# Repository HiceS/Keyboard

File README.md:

# Keyboard
Keyboard pcb

## Description
Uses ` 104 ` key keyboard design, can be shortened

    ["Esc",{x:1},"F1","F2","F3","F4",{x:0.5},"F5","F6","F7","F8",{x:0.5},"F9","F10","F11","F12",{x:0.25},"PrtSc","Scroll Lock","Pause\nBreak"],
    [{y:0.5},"~\n`","!\n1","@\n2","#\n3","$\n4","%\n5","^\n6","&\n7","*\n8","(\n9",")\n0","_\n-","+\n=",{w:2},"Backspace",{x:0.25},"Insert","Home","PgUp",{x:0.25},"Num Lock","/","*","-"],
    [{w:1.5},"Tab","Q","W","E","R","T","Y","U","I","O","P","{\n[","}\n]",{w:1.5},"|\n\\",{x:0.25},"Delete","End","PgDn",{x:0.25},"7\nHome","8\n↑","9\nPgUp",{h:2},"+"],
    [{w:1.75},"Caps Lock","A","S","D","F","G","H","J","K","L",":\n;","\"\n'",{w:2.25},"Enter",{x:3.5},"4\n←","5","6\n→"],
    [{w:2.25},"Shift","Z","X","C","V","B","N","M","<\n,",">\n.","?\n/",{w:2.75},"Shift",{x:1.25},"↑",{x:1.25},"1\nEnd","2\n↓","3\nPgDn",{h:2},"Enter"],
    [{w:1.25},"Ctrl",{w:1.25},"Win",{w:1.25},"Alt",{a:7,w:6.25},"",{a:4,w:1.25},"Alt",{w:1.25},"Win",{w:1.25},"Menu",{w:1.25},"Ctrl",{x:0.25},"←","↓","→",{x:0.25,w:2},"0\nIns",".\nDel"]

#### Example Layout

#### Plans to have:
- Fusion 360 Case and Board Design
- Generative Design Case
- Stress Simulations

## How to use
The ` .brd ` & ` .sch ` Files are from **Autodesk Eagle**

Open the parent folder in Eagle and you can see the schematic and board design.

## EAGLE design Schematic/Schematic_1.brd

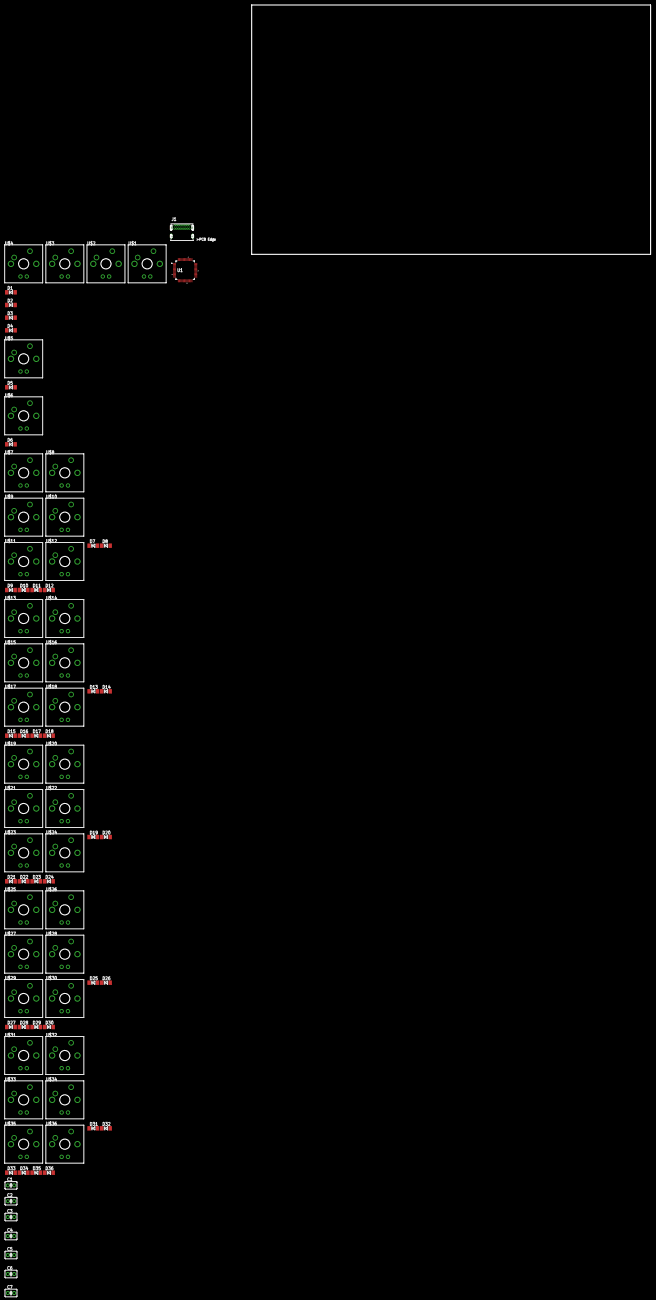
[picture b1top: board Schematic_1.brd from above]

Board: 2 copper layers, 192.6 x 100.0 mm, 81 parts (0 on the bottom side), 54 nets, no tracks yet.

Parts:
C1, C2, C4: 100 nF; C2.5-3
C3, C5: 4.7 mF; C2.5-3
C6: 10 nF; C2.5-3
C7: 1 mF; C2.5-3
D1, D2, D3, D4, D5, D6, D7, D8, D9, D10, D11, D12, D13, D14, D15, D16, D17, D18, D19, D20, D21, D22, D23, D24, D25, D26, D27, D28, D29, D30, D31, D32, D33, D34, D35, D36: SOD80C
J1: USB4085-GF-A_REVA; GCT_USB4085-GF-A_REVA
U1: STM32F0XXC2T; LQFP48-7X7MM
U$1, U$2, U$3, U$4, U$5, U$6, U$7, U$8, U$9, U$10, U$11, U$12, U$13, U$14, U$15, U$16, U$17, U$18, U$19, U$20, U$21, U$22, U$23, U$24, U$25, U$26, U$27, U$28, U$29, U$30, U$31, U$32, U$33, U$34, U$35, U$36: CHERRY-MX-LED

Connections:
COL1: D1.C, D2.C, D3.C, D4.C, D5.C, D6.C, U1.41
COL2: D7.C, D8.C, D9.C, D10.C, D11.C, D12.C, U1.40
COL3: D13.C, D14.C, D15.C, D16.C, D17.C, D18.C, U1.39
COL4: D19.C, D20.C, D21.C, D22.C, D23.C, D24.C, U1.20
COL5: D25.C, D26.C, D27.C, D28.C, D29.C, D30.C, U1.19
COL6: D31.C, D32.C, D33.C, D34.C, D35.C, D36.C, U1.18
unnamed: D2.A, U$1.SW2
unnamed: D1.A, U$3.SW2
unnamed: D3.A, U$4.SW2
unnamed: D6.A, U$6.SW2
unnamed: D8.A, U$7.SW2
unnamed: D4.A, U$2.SW2
unnamed: D5.A, U$5.SW2
unnamed: D7.A, U$9.SW2
unnamed: D9.A, U$10.SW2
unnamed: D10.A, U$8.SW2
unnamed: D11.A, U$11.SW2
unnamed: D12.A, U$12.SW2
unnamed: D14.A, U$13.SW2
unnamed: D13.A, U$15.SW2
unnamed: D15.A, U$16.SW2
unnamed: D16.A, U$14.SW2
unnamed: D17.A, U$17.SW2
unnamed: D18.A, U$18.SW2
unnamed: D20.A, U$19.SW2
unnamed: D19.A, U$21.SW2
unnamed: D21.A, U$22.SW2
unnamed: D22.A, U$20.SW2
unnamed: D23.A, U$23.SW2
unnamed: D24.A, U$24.SW2
unnamed: D26.A, U$25.SW2
unnamed: D25.A, U$27.SW2
unnamed: D27.A, U$28.SW2
unnamed: D28.A, U$26.SW2
unnamed: D29.A, U$29.SW2
unnamed: D30.A, U$30.SW2
unnamed: D32.A, U$31.SW2
unnamed: D31.A, U$33.SW2
unnamed: D33.A, U$34.SW2
unnamed: D34.A, U$32.SW2
unnamed: D35.A, U$35.SW2
unnamed: D36.A, U$36.SW2
unnamed: C1.1, C4.2, C6.2, J1.A4, J1.A9, J1.B4, J1.B9, U1.9, U1.24, U1.36
unnamed: C2.2, C3.1
unnamed: C1.2, C2.1
unnamed: C3.2, C5.1, C7.1, J1.A1, J1.A12, J1.B1, J1.B12, U1.8, U1.47, U1.48
unnamed: C4.1, C5.2
unnamed: C6.1, C7.2
ROW1: U1.42, U$1.SW1, U$7.SW1, U$13.SW1
ROW2: U1.43, U$3.SW1, U$9.SW1, U$15.SW1
ROW3: U1.45, U$4.SW1, U$10.SW1, U$16.SW1
ROW4: U1.46, U$2.SW1, U$8.SW1, U$14.SW1
ROW5: U1.21, U$5.SW1, U$11.SW1, U$17.SW1
ROW6: U1.22, U$6.SW1, U$12.SW1, U$18.SW1

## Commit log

2019-09-01 Added original PCB
2019-09-08 Added Power Supply hopefully correctly
2019-09-08 Removed the extra line for programming
2019-09-08 Added README, changed folder structure
2019-09-08 halp
2019-09-08 updated power supply stuff
2019-09-12 Added hopefully correct power supply lines
2019-09-12 removed redundancy
